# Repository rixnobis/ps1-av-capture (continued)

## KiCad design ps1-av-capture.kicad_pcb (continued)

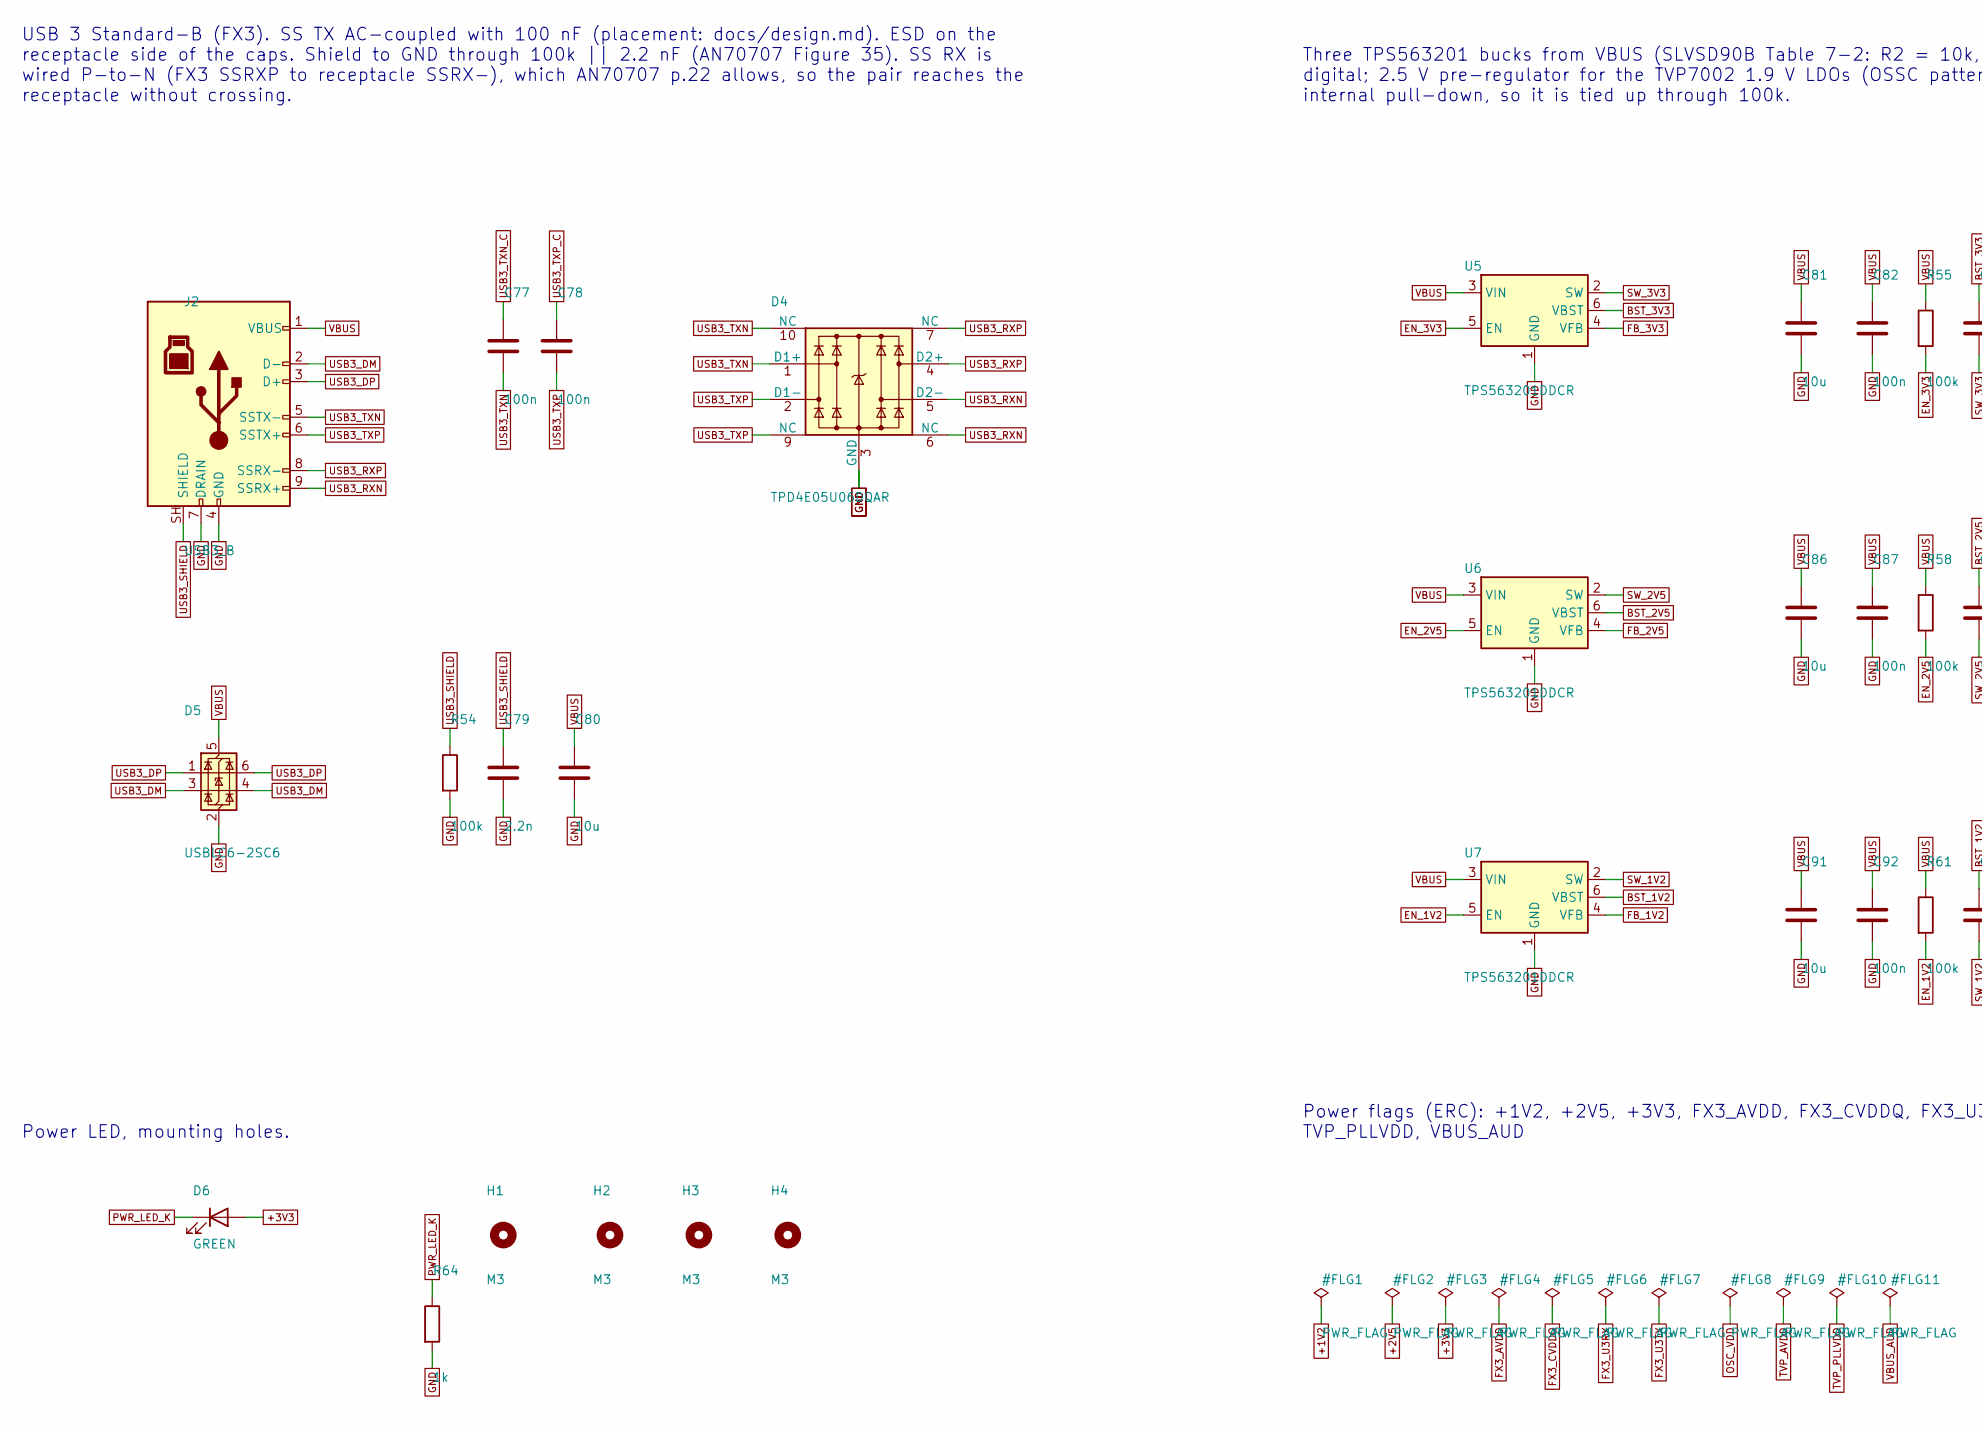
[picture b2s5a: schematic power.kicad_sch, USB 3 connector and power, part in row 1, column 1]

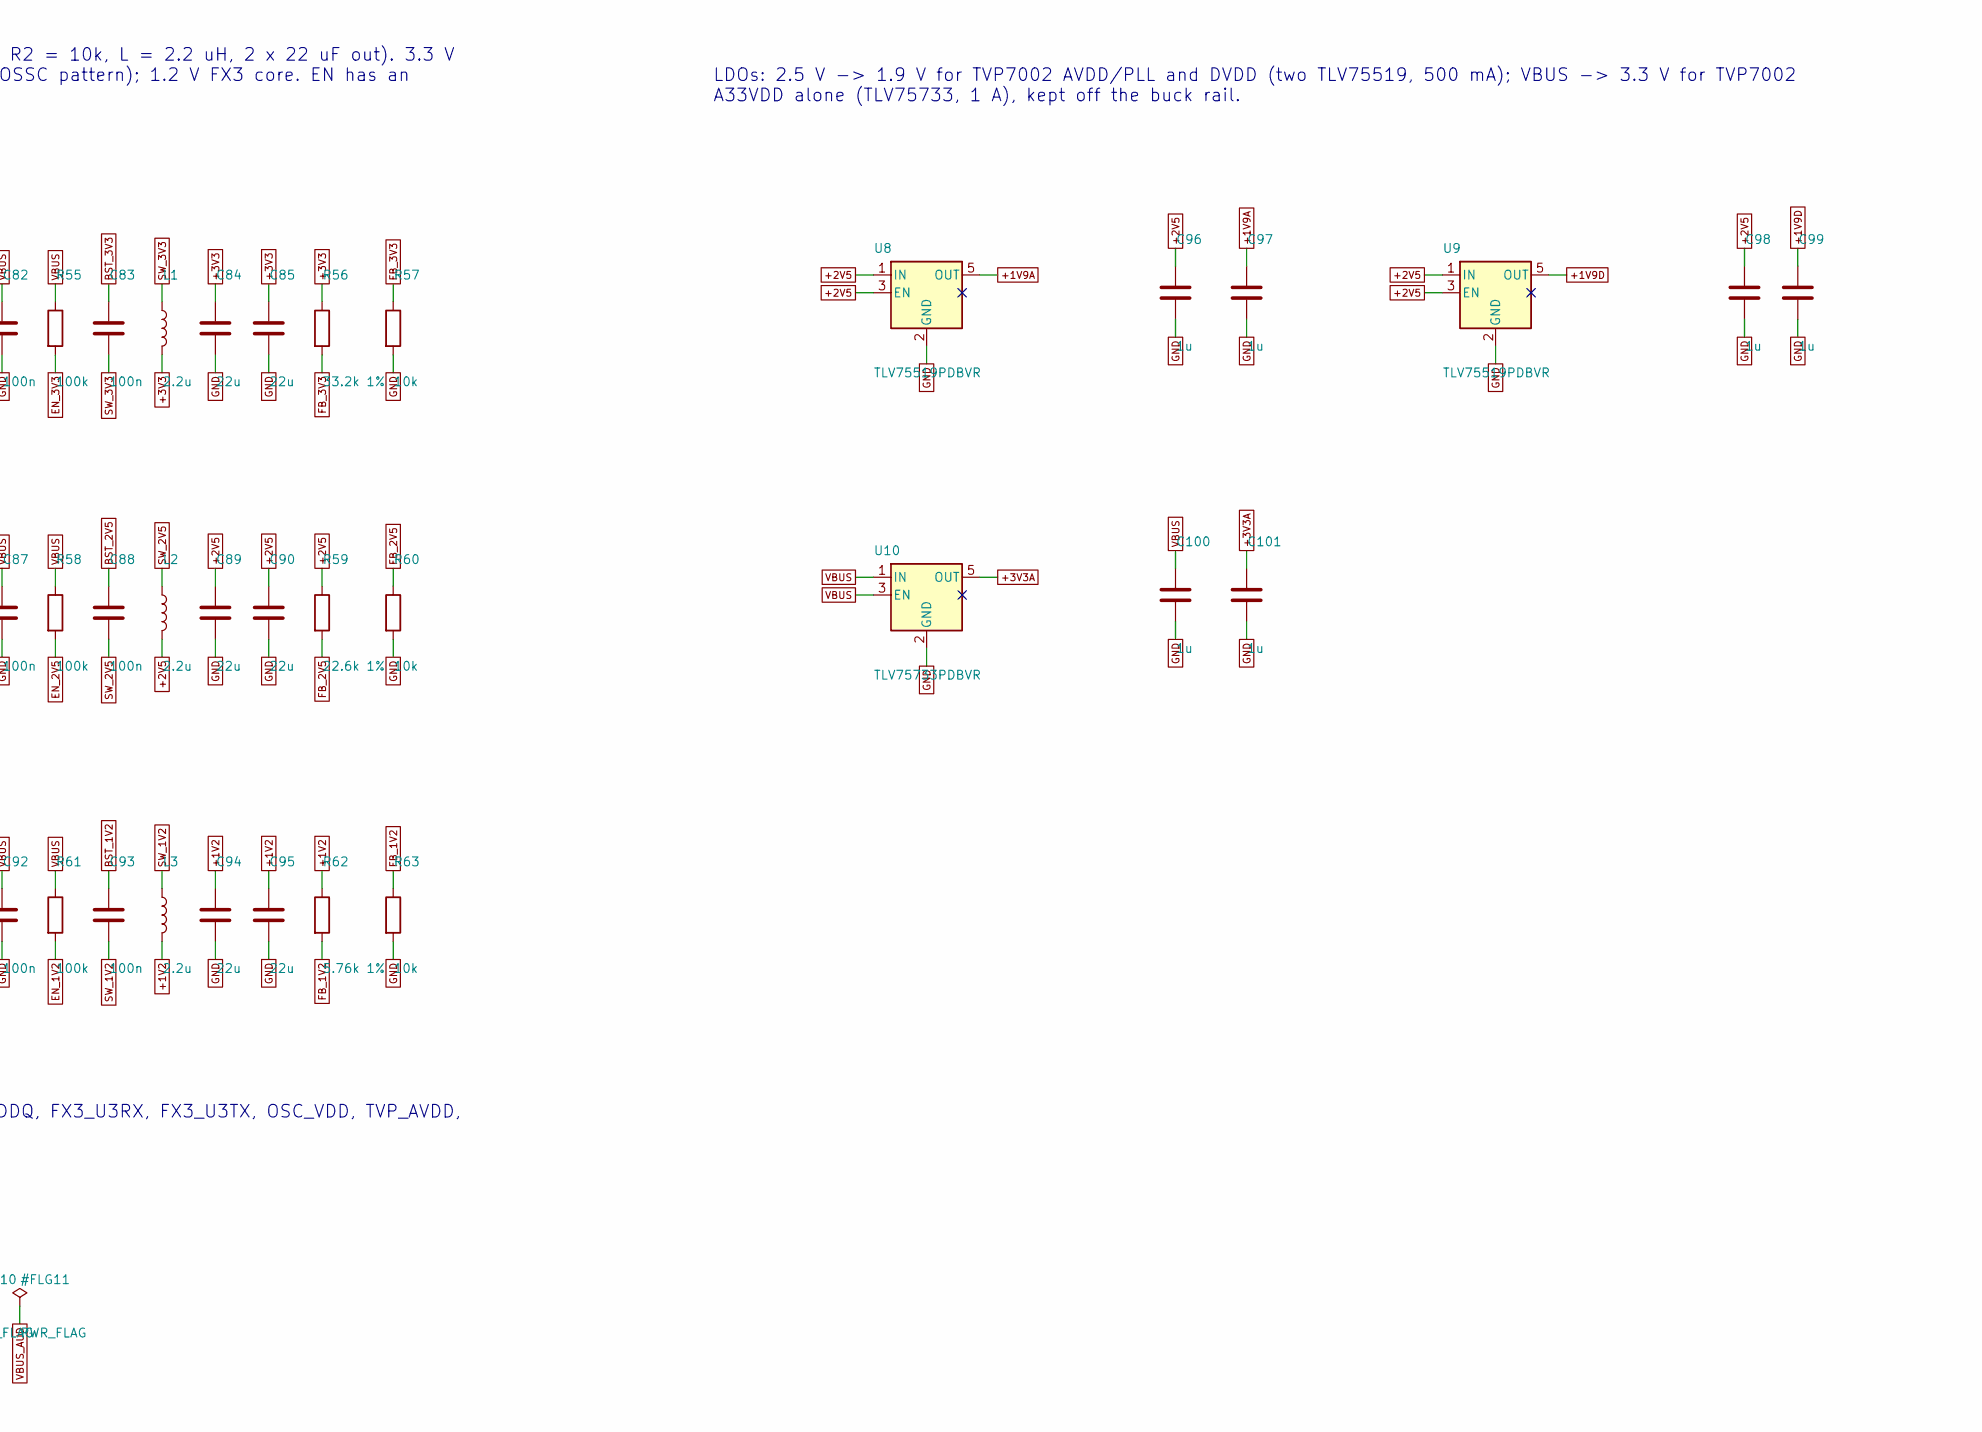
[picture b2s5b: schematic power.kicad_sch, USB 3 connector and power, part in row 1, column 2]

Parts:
C77, C78, C82, C83, C87, C88, C92, C93: 100n; C_0402_1005Metric; LCSC C1525
C79: 2.2n; C_0402_1005Metric; LCSC C1531
C80, C81, C86, C91: 10u; C_0603_1608Metric; LCSC C19702
C84, C85, C89, C90, C94, C95: 22u; C_0805_2012Metric; LCSC C45783
C96, C97, C98, C99, C100, C101: 1u; C_0402_1005Metric; LCSC C52923
D4: TPD4E05U06DQAR; USON-10_2.5x1.0mm_P0.5mm; LCSC C138714
D5: USBLC6-2SC6; SOT-23-6; LCSC C7519
D6: GREEN; LED_0603_1608Metric; LCSC C2986059
H1, H2, H3, H4: M3; MountingHole_3.2mm_M3
J2: USB3_B; USB-B-TH_9P-L18.5-W12.0; LCSC C7501849
L1, L2, L3: 2.2u; L_Sunlord_SWPA4030S; LCSC C36409
R54, R55, R58, R61: 100k; R_0402_1005Metric; LCSC C25741
R56: 33.2k 1%; R_0402_1005Metric; LCSC C122548
R57, R60, R63: 10k; R_0402_1005Metric; LCSC C25744
R59: 22.6k 1%; R_0402_1005Metric; LCSC C26960
R62: 5.76k 1%; R_0402_1005Metric; LCSC C5153969
R64: 1k; R_0402_1005Metric; LCSC C11702
U5, U6, U7: TPS563201DDCR; SOT-23-6_L2.9-W1.6-P0.95-LS2.8-BR; LCSC C116592
U8, U9: TLV75519PDBVR; SOT-23-5; LCSC C2865381
U10: TLV75733PDBVR; SOT-23-5; LCSC C485517

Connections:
+1V2: C94.1, C95.1, L3.2, R62.1; also elsewhere on the board
+1V9A: C97.1, U8.5 (OUT); also elsewhere on the board
+1V9D: C99.1, U9.5 (OUT); also elsewhere on the board
+2V5: C89.1, C90.1, C96.1, C98.1, L2.2, R59.1, U8.1 (IN), U8.3 (EN), U9.1 (IN), U9.3 (EN)
+3V3: C84.1, C85.1, D6.2 (A), L1.2, R56.1; also elsewhere on the board
+3V3A: C101.1, U10.5 (OUT); also elsewhere on the board
BST_1V2: C93.1, U7.6 (VBST)
BST_2V5: C88.1, U6.6 (VBST)
BST_3V3: C83.1, U5.6 (VBST)
EN_1V2: R61.2, U7.5 (EN)
EN_2V5: R58.2, U6.5 (EN)
EN_3V3: R55.2, U5.5 (EN)
FB_1V2: R62.2, R63.1, U7.4 (VFB)
FB_2V5: R59.2, R60.1, U6.4 (VFB)
FB_3V3: R56.2, R57.1, U5.4 (VFB)
GND: C79.2, C80.2, C81.2, C82.2, C84.2, C85.2, C86.2, C87.2, C89.2, C90.2, C91.2, C92.2, C94.2, C95.2, C96.2, C97.2, C98.2, C99.2, C100.2, C101.2, D4.3 (GND), D4.8 (GND), D5.2 (GND), J2.4 (GND), J2.7 (DRAIN), R54.2, R57.2, R60.2, R63.2, R64.2, U5.1 (GND), U6.1 (GND), U7.1 (GND), U8.2 (GND), U9.2 (GND), U10.2 (GND); also elsewhere on the board
PWR_LED_K: D6.1 (K), R64.1
SW_1V2: C93.2, L3.1, U7.2 (SW)
SW_2V5: C88.2, L2.1, U6.2 (SW)
SW_3V3: C83.2, L1.1, U5.2 (SW)
USB3_DM: D5.3 (I/O2), D5.4 (I/O2), J2.2 (D-); also elsewhere on the board
USB3_DP: D5.1 (I/O1), D5.6 (I/O1), J2.3 (D+); also elsewhere on the board
USB3_RXN: D4.5 (D2-), D4.6 (NC), J2.9 (SSRX+); also elsewhere on the board
USB3_RXP: D4.4 (D2+), D4.7 (NC), J2.8 (SSRX-); also elsewhere on the board
USB3_SHIELD: C79.1, J2.SH (SHIELD), R54.1
USB3_TXN: C77.2, D4.1 (D1+), D4.10 (NC), J2.5 (SSTX-)
USB3_TXN_C: C77.1; also elsewhere on the board
USB3_TXP: C78.2, D4.2 (D1-), D4.9 (NC), J2.6 (SSTX+)
USB3_TXP_C: C78.1; also elsewhere on the board
VBUS: C80.1, C81.1, C82.1, C86.1, C87.1, C91.1, C92.1, C100.1, D5.5 (VBUS), J2.1 (VBUS), R55.1, R58.1, R61.1, U5.3 (VIN), U6.3 (VIN), U7.3 (VIN), U10.1 (IN), U10.3 (EN); also elsewhere on the board

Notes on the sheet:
USB 3 Standard-B (FX3). SS TX AC-coupled with 100 nF (placement: docs/design.md). ESD on the receptacle side of the caps. Shield to GND through 100k || 2.2 nF (AN70707 Figure 35). SS RX is wired P-to-N (FX3 SSRXP to receptacle SSRX-), which AN70707 p.22 allows, so the pair reaches the receptacle wi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
Three TPS563201 bucks from VBUS (SLVSD90B Table 7-2: R2 = 10k, L = 2.2 uH, 2 x 22 uF out). 3.3 V digital; 2.5 V pre-regulator for the TVP7002 1.9 V LDOs (OSSC pattern); 1.2 V FX3 core. EN has an internal pull-down, so it is tied up through 100k.
LDOs: 2.5 V -> 1.9 V for TVP7002 AVDD/PLL and DVDD (two TLV75519, 500 mA); VBUS -> 3.3 V for TVP7002 A33VDD alone (TLV75733, 1 A), kept off the buck rail.
Power LED, mounting holes.
Power flags (ERC): +1V2, +2V5, +3V3, FX3_AVDD, FX3_CVDDQ, FX3_U3RX, FX3_U3TX, OSC_VDD, TVP_AVDD, TVP_PLLVDD, VBUS_AUD

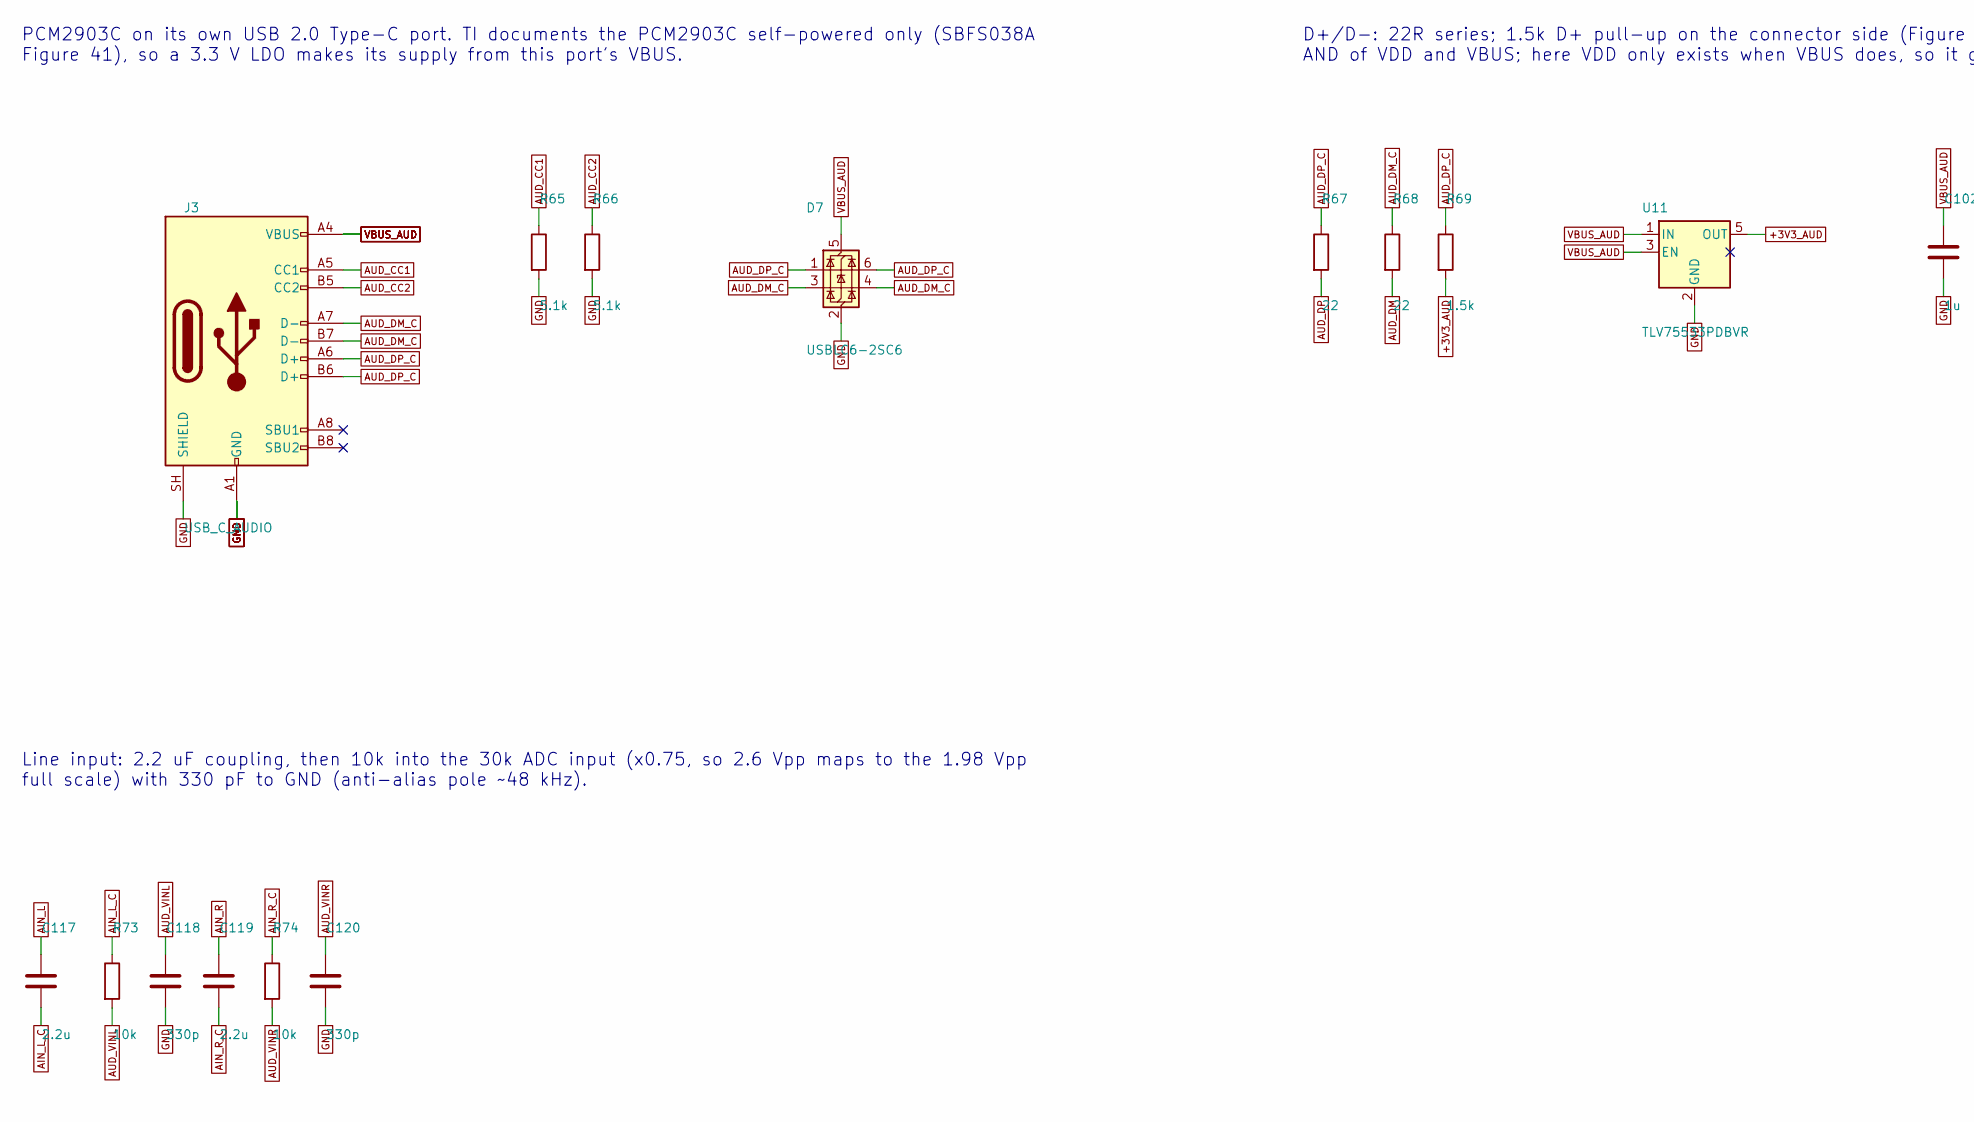
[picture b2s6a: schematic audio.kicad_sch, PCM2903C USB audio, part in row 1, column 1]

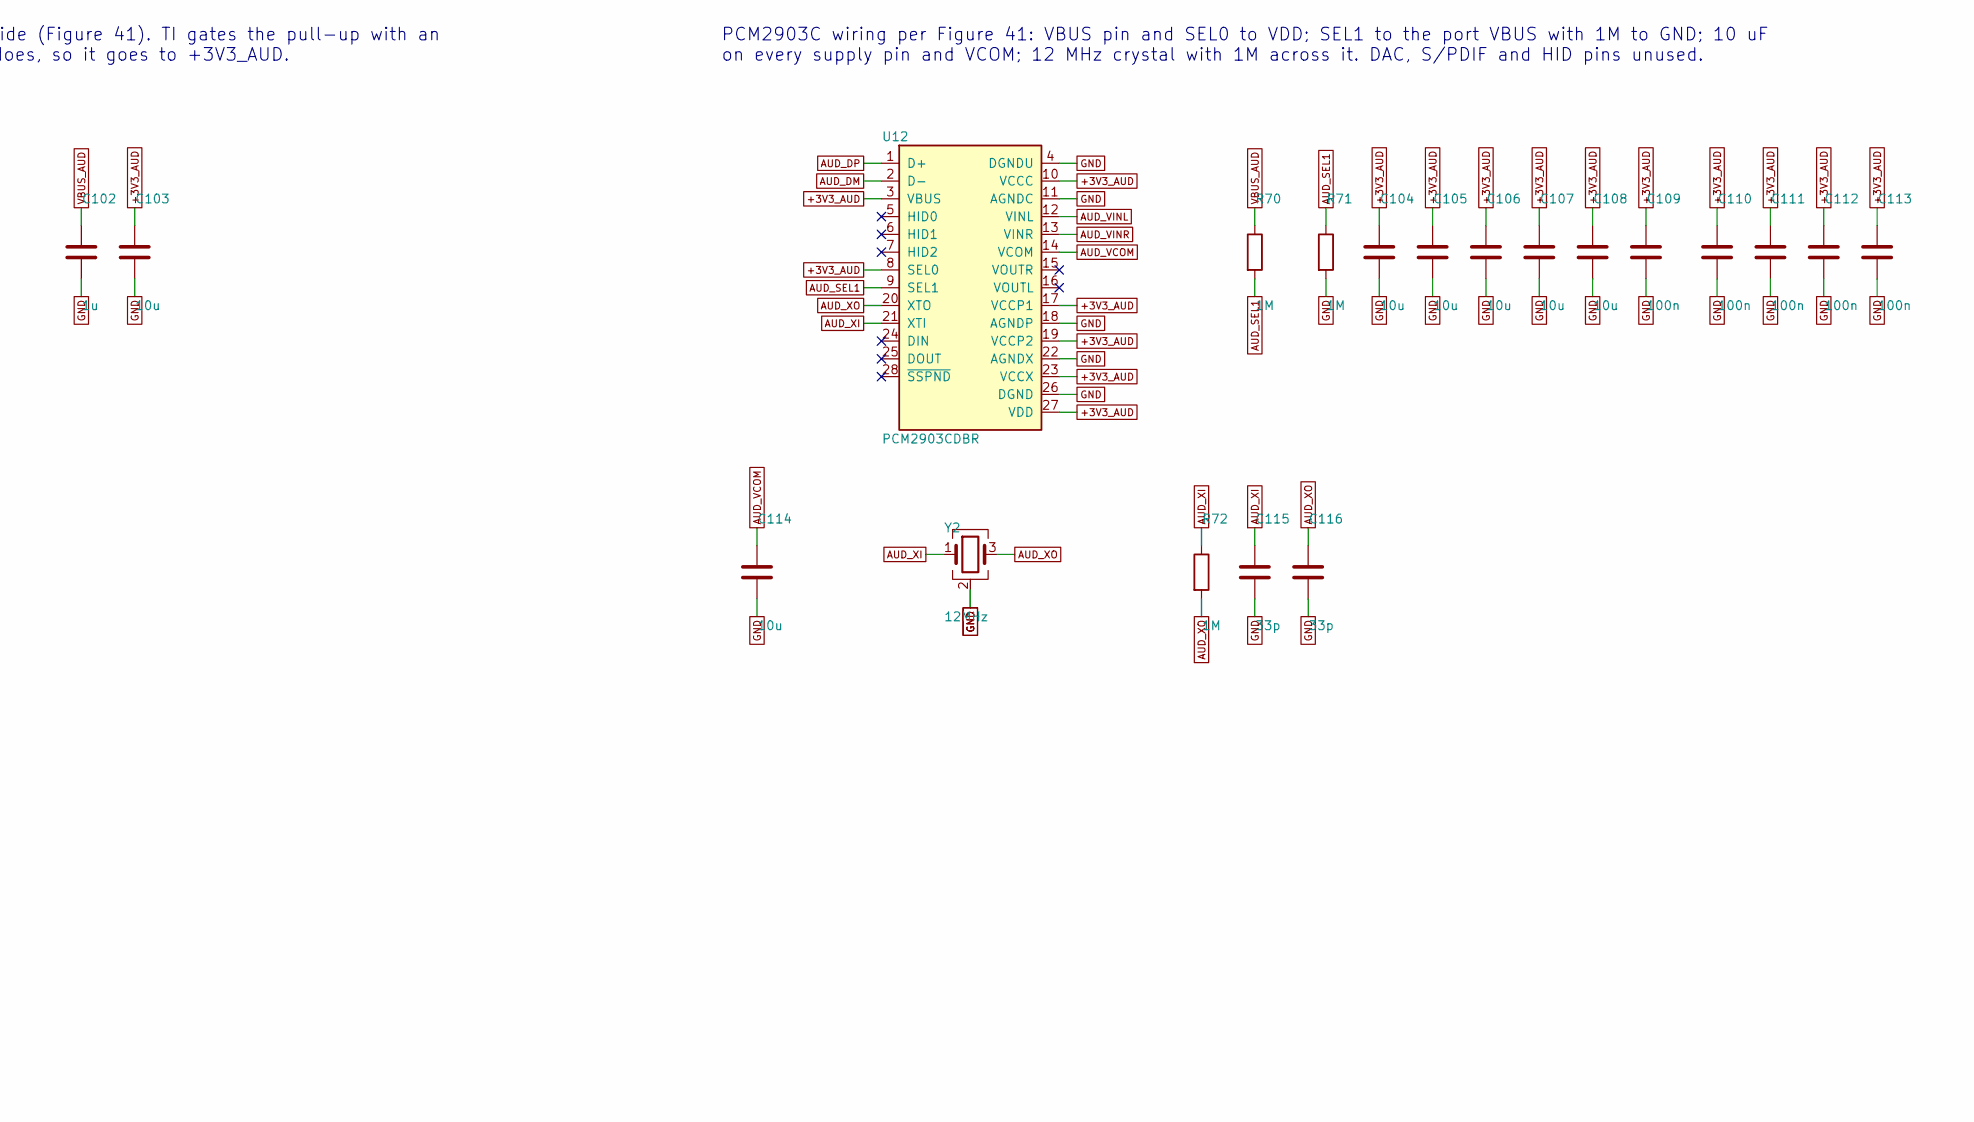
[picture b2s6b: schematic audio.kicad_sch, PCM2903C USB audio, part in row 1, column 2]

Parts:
C102: 1u; C_0402_1005Metric; LCSC C52923
C103, C104, C105, C106, C107, C108, C114: 10u; C_0603_1608Metric; LCSC C19702
C109, C110, C111, C112, C113: 100n; C_0402_1005Metric; LCSC C1525
C115, C116: 33p; C_0402_1005Metric; LCSC C1562
C117, C119: 2.2u; C_0603_1608Metric; LCSC C23630
C118, C120: 330p; C_0402_1005Metric; LCSC C13533
D7: USBLC6-2SC6; SOT-23-6; LCSC C7519
J3: USB_C_AUDIO; USB_C_Receptacle_HRO_TYPE-C-31-M-12; LCSC C165948
R65, R66: 5.1k; R_0402_1005Metric; LCSC C25905
R67, R68: 22; R_0402_1005Metric; LCSC C25092
R69: 1.5k; R_0402_1005Metric; LCSC C25867
R70, R71, R72: 1M; R_0402_1005Metric; LCSC C26083
R73, R74: 10k; R_0402_1005Metric; LCSC C25744
U11: TLV75533PDBVR; SOT-23-5; LCSC C404027
U12: PCM2903CDBR; SSOP-28_5.3x10.2mm_P0.65mm; LCSC C2861593
Y2: 12MHz; Crystal_SMD_3225-4Pin_3.2x2.5mm; LCSC C9002

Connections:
+3V3_AUD: C103.1, C104.1, C105.1, C106.1, C107.1, C108.1, C109.1, C110.1, C111.1, C112.1, C113.1, R69.2, U11.5 (OUT), U12.3 (VBUS), U12.8 (SEL0), U12.10 (VCCC), U12.17 (VCCP1), U12.19 (VCCP2), U12.23 (VCCX), U12.27 (VDD)
AIN_L: C117.1; also elsewhere on the board
AIN_L_C: C117.2, R73.1; also elsewhere on the board
AIN_R: C119.1; also elsewhere on the board
AIN_R_C: C119.2, R74.1; also elsewhere on the board
AUD_CC1: J3.A5 (CC1), R65.1
AUD_CC2: J3.B5 (CC2), R66.1
AUD_DM: R68.2, U12.2 (D-)
AUD_DM_C: D7.3 (I/O2), D7.4 (I/O2), J3.A7 (D-), J3.B7 (D-), R68.1
AUD_DP: R67.2, U12.1 (D+)
AUD_DP_C: D7.1 (I/O1), D7.6 (I/O1), J3.A6 (D+), J3.B6 (D+), R67.1, R69.1
AUD_SEL1: R70.2, R71.1, U12.9 (SEL1)
AUD_VCOM: C114.1, U12.14 (VCOM)
AUD_VINL: C118.1, R73.2, U12.12 (VINL)
AUD_VINR: C120.1, R74.2, U12.13 (VINR)
AUD_XI: C115.1, R72.1, U12.21 (XTI), Y2.1
AUD_XO: C116.1, R72.2, U12.20 (XTO), Y2.3
GND: C102.2, C103.2, C104.2, C105.2, C106.2, C107.2, C108.2, C109.2, C110.2, C111.2, C112.2, C113.2, C114.2, C115.2, C116.2, C118.2, C120.2, D7.2 (GND), J3.A1 (GND), J3.A12 (GND), J3.B1 (GND), J3.B12 (GND), J3.SH (SHIELD), R65.2, R66.2, R71.2, U11.2 (GND), U12.4 (DGNDU), U12.11 (AGNDC), U12.18 (AGNDP), U12.22 (AGNDX), U12.26 (DGND), Y2.2 (G), Y2.4 (G); also elsewhere on the board
VBUS_AUD: C102.1, D7.5 (VBUS), J3.A4 (VBUS), J3.A9 (VBUS), J3.B4 (VBUS), J3.B9 (VBUS), R70.1, U11.1 (IN), U11.3 (EN)

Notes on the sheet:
PCM2903C on its own USB 2.0 Type-C port. TI documents the PCM2903C self-powered only (SBFS038A Figure 41), so a 3.3 V LDO makes its supply from this port's VBUS.
D+/D-: 22R series; 1.5k D+ pull-up on the connector side (Figure 41). TI gates the pull-up with an AND of VDD and VBUS; here VDD only exists when VBUS does, so it goes to +3V3_AUD.
PCM2903C wiring per Figure 41: VBUS pin and SEL0 to VDD; SEL1 to the port VBUS with 1M to GND; 10 uF on every supply pin and VCOM; 12 MHz crystal with 1M across it. DAC, S/PDIF and HID pins unused.
Line input: 2.2 uF coupling, then 10k into the 30k ADC input (x0.75, so 2.6 Vpp maps to the 1.98 Vpp full scale) with 330 pF to GND (anti-alias pole ~48 kHz).

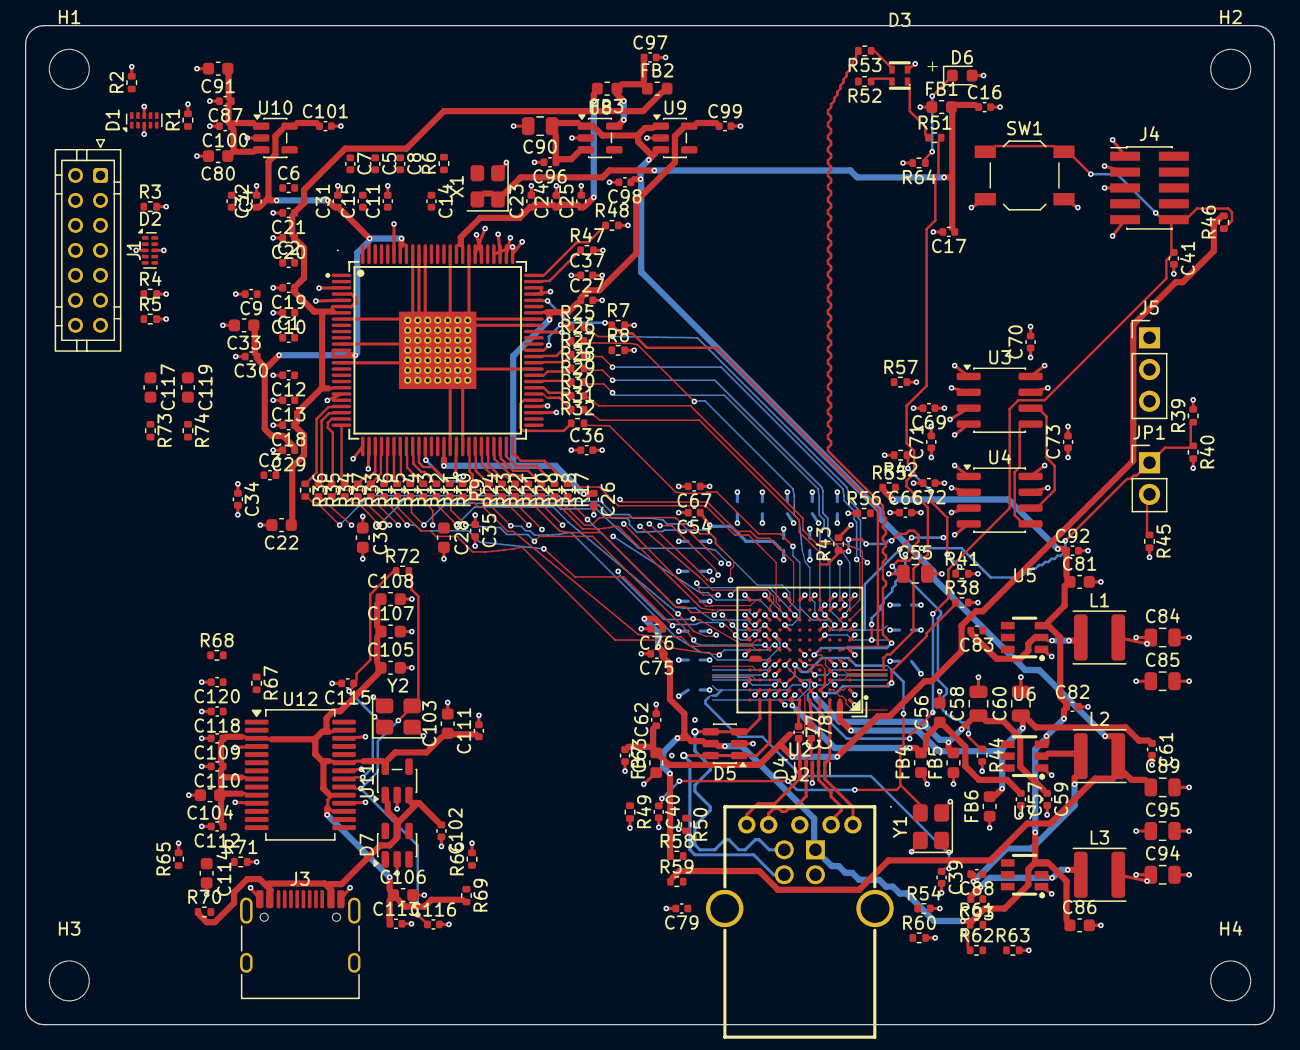
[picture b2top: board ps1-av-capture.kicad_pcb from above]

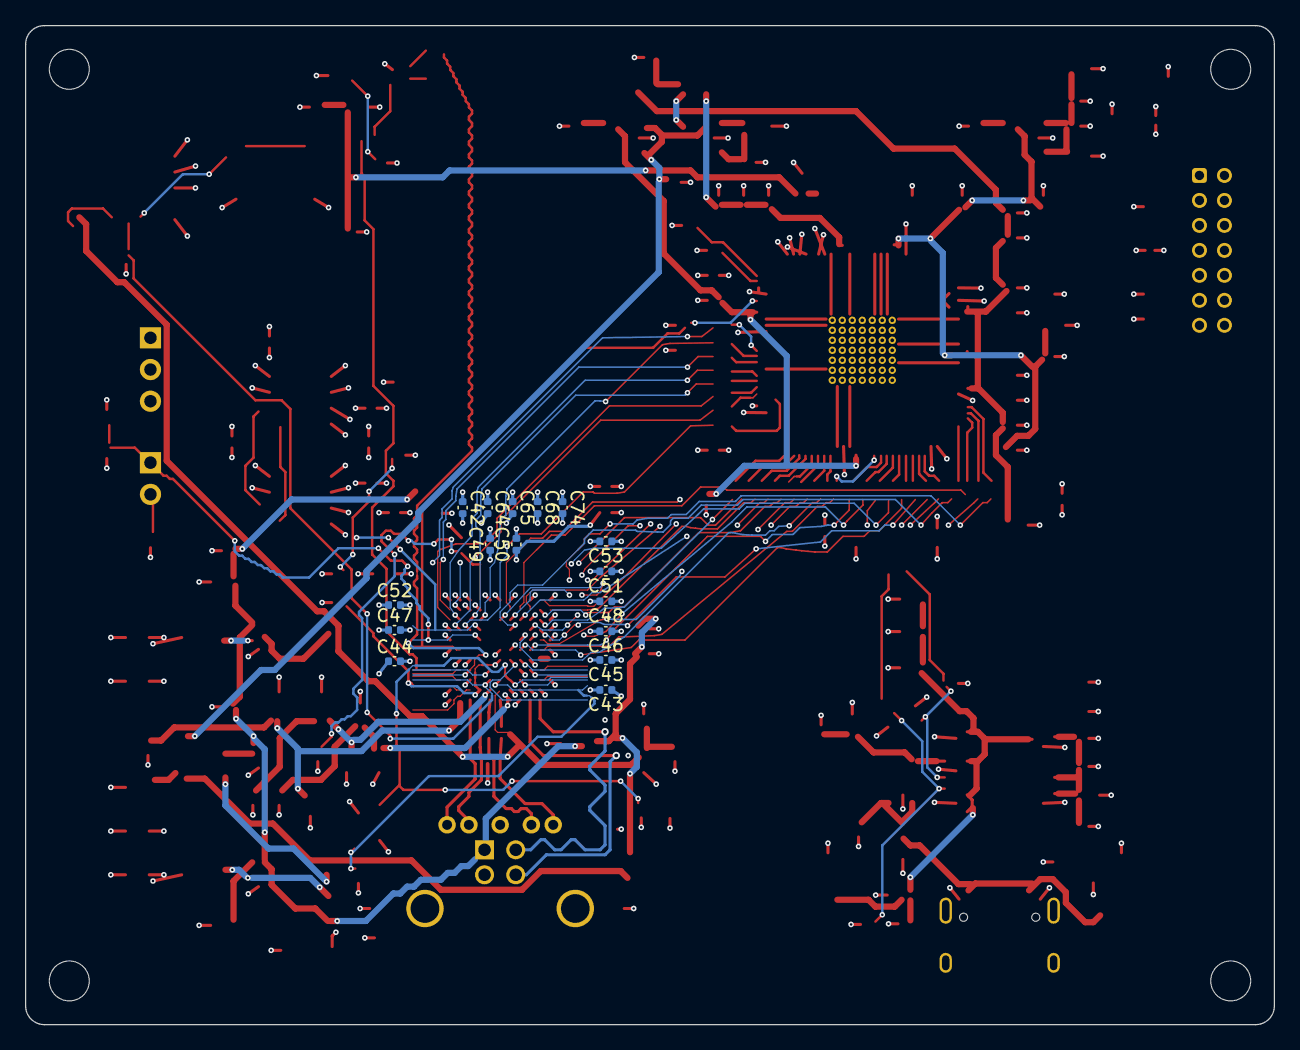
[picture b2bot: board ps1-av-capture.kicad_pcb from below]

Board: 4 copper layers, 100.0 x 80.0 mm, 237 parts (16 on the bottom side), 162 nets.

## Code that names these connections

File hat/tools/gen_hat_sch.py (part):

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# Pin -> CH32H417 port, as wired by the Maker go CH32H417QEU6 headers. Pins not listed are open.
# Column-wise numbering: column k holds pins 3k-2, 3k-1, 3k.
#   J4 (U12): 1-3 DCDC_VIN (unused)  4-6,13-16 GND  7-9 +5V  10-12 +3V3
#     17 MCU_RD_N  PB11     18 MCU_RDNE PB10     20 MCU_WRNF PE14     24 MCU_AF_N PE10
#     28 I2C_SDA   PF13     29 I2C_SCL  PF12     30 VD_PCLK  PF11
#     43 VD_HS     PA0      42 VD_VS    PA1      41 VD_FID   PA2      40 VD_SOG   PA3
#     39 TVP_RESETn PA4     38 CAP_EN_N PA5
#   J5 (U13): 1 MCU_OE_N PB12   2 UHSIF_WR_N PB13   3 UHSIF_CS_N PB14
#     7 VD_Y0 PD10   8 VD_Y1 PD11   9 VD_Y2 PD12   10 VD_Y3 PD13   11 VD_Y4 PD14   12 VD_Y5 PD15
#     13 VD_Y6 PF0   14 VD_Y7 PF1   15 VD_C0 PF2   16 VD_C1 PC6    17 VD_C2 PC7    18 VD_C3 PC8
#     19 VD_C4 PC9   25 VD_C5 PA13  26 VD_C6 PA14  27 VD_C7 PA15
J4_NETS = {1: None, 2: None, 3: None, 4: "GND", 5: "GND", 6: "GND", 7: "+5V", 8: "+5V", 9: "+5V",
           10: "+3V3", 11: "+3V3", 12: "+3V3", 13: "GND", 14: "GND", 15: "GND", 16: "GND",
           17: "MCU_RD_N", 18: "MCU_RDNE", 20: "MCU_WRNF", 24: "MCU_AF_N",
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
